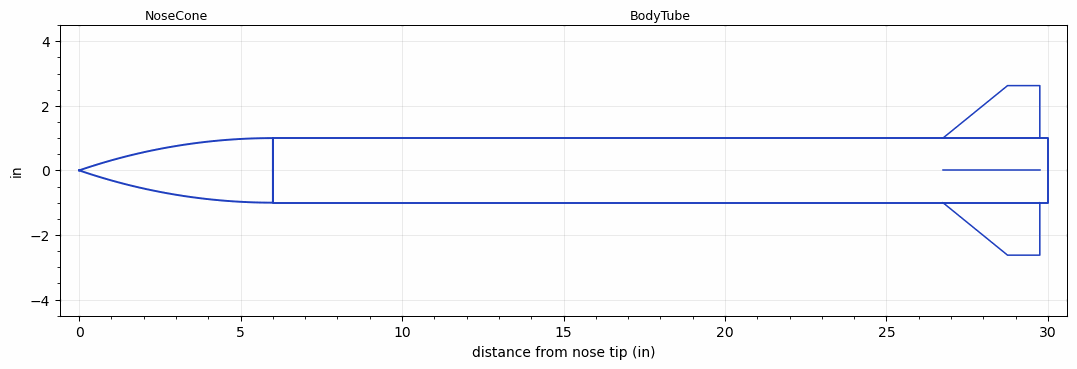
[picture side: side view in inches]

<RASAeroDocument>
 <FileVersion>2</FileVersion>
 <RocketDesign>
  <NoseCone>
   <Length>6.0</Length>
   <Diameter>2.0</Diameter>
   <Shape>Tangent Ogive</Shape>
   <Location>0.0</Location>
  </NoseCone>
  <BodyTube>
   <Length>23.99995</Length>
   <Diameter>2.0</Diameter>
   <Location>6.0</Location>
   <Fin>
    <Count>4</Count>
    <Chord>3.0</Chord>
    <Span>1.625</Span>
    <SweepDistance>2.0</SweepDistance>
    <TipChord>1.0</TipChord>
    <Thickness>0.0625</Thickness>
    <Location>3.25</Location>
    <AirfoilSection>Hexagonal Blunt Base</AirfoilSection>
    <FX1>0.125</FX1>
   </Fin>
  </BodyTube>
  <Surface>Smooth (Zero Roughness)</Surface>
  <ModifiedBarrowman>False</ModifiedBarrowman>
  <Turbulence>True</Turbulence>
  <UseBooster1>False</UseBooster1>
  <UseBooster2>False</UseBooster2>
  <Comments>Extended controlled aerodynamic study: Hbev-scale0.5</Comments>
 </RocketDesign>
 <LaunchSite>
  <Altitude>0</Altitude>
  <Pressure>29.9214</Pressure>
  <RodAngle>0</RodAngle>
  <RodLength>6.5617</RodLength>
  <Temperature>59</Temperature>
  <WindSpeed>0</WindSpeed>
 </LaunchSite>
 <Recovery>
  <Altitude1>656.168</Altitude1>
  <Altitude2>0</Altitude2>
  <DeviceType1>Parachute</DeviceType1>
  <DeviceType2>None</DeviceType2>
  <Event1>True</Event1>
  <Event2>False</Event2>
  <Size1>24</Size1>
  <Size2>0</Size2>
  <EventType1>Apogee</EventType1>
  <EventType2>None</EventType2>
  <CD1>0.8</CD1>
  <CD2>0</CD2>
 </Recovery>
 <SimulationList>
  <Simulation>
   <SustainerEngine>I500T-14A  (AT)</SustainerEngine>
   <SustainerLaunchWt>14.5064</SustainerLaunchWt>
   <SustainerCG>34.7639</SustainerCG>
   <SustainerIgnitionDelay>0</SustainerIgnitionDelay>
   <Booster1SeparationDelay>0</Booster1SeparationDelay>
   <Booster1IgnitionDelay>0</Booster1IgnitionDelay>
   <IncludeBooster1>False</IncludeBooster1>
   <Booster2Delay>0</Booster2Delay>
   <IncludeBooster2>False</IncludeBooster2>
   <TimetoApogee>9.190115</TimetoApogee>
   <MaxAltitude>1235.54</MaxAltitude>
   <MaxVelocity>270.5551</MaxVelocity>
  </Simulation>
  <Simulation>
   <SustainerEngine>J570W  (AT)</SustainerEngine>
   <SustainerLaunchWt>15.1813</SustainerLaunchWt>
   <SustainerCG>35.261</SustainerCG>
   <SustainerIgnitionDelay>0</SustainerIgnitionDelay>
   <Booster1SeparationDelay>0</Booster1SeparationDelay>
   <Booster1IgnitionDelay>0</Booster1IgnitionDelay>
   <IncludeBooster1>False</IncludeBooster1>
   <Booster2Delay>0</Booster2Delay>
   <IncludeBooster2>False</IncludeBooster2>
   <TimetoApogee>13.66022</TimetoApogee>
   <MaxAltitude>2940.604</MaxAltitude>
   <MaxVelocity>432.8058</MaxVelocity>
  </Simulation>
 </SimulationList>
</RASAeroDocument>
